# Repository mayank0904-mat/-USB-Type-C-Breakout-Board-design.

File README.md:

# USB Type-C Breakout Board

## Description
A compact USB Type-C breakout board designed using KiCad.

## Features
- USB Type-C Connector
- Through-hole breakout pins
- DRC Clean Design
- Gerber Files Included

## Software Used
- KiCad

## Author
Mayank Mathur

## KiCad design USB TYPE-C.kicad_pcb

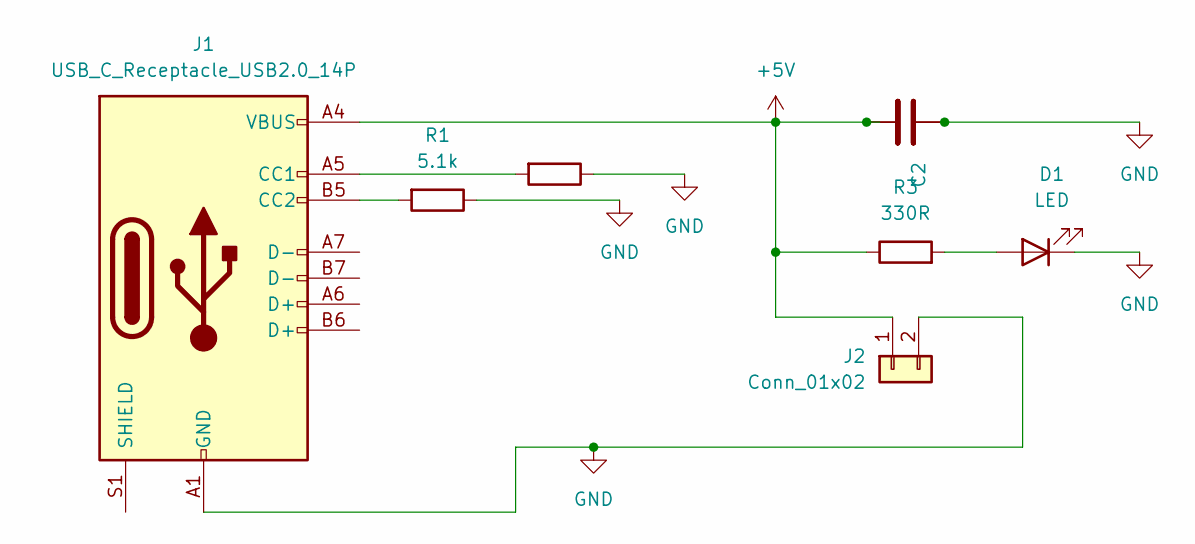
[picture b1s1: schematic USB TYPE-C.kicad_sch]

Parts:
C1: C; C_0805_2012Metric
C2: 10uf; C_0805_2012Metric
D1: LED; LED_0805_2012Metric
J1: USB_C_Receptacle_USB2.0_14P; USB_C_Receptacle_HRO_TYPE-C-31-M-12
J2: Conn_01x02; PinHeader_1x02_P2.54mm_Vertical
R1, R2: 5.1k; R_0805_2012Metric
R3: 330R; R_0805_2012Metric

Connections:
+5V: C1.2, C2.2, J1.A4 (VBUS), J1.A9 (VBUS), J1.B4 (VBUS), J1.B9 (VBUS), J2.1, R3.1
GND: C1.1, C2.1, D1.1 (K), J1.A1 (GND), J1.A12 (GND), J1.B1 (GND), J1.B12 (GND), J2.2, R1.1, R2.1
unnamed: D1.2 (A), R3.2
unnamed: J1.A5 (CC1), R2.2
unnamed: J1.B5 (CC2), R1.2

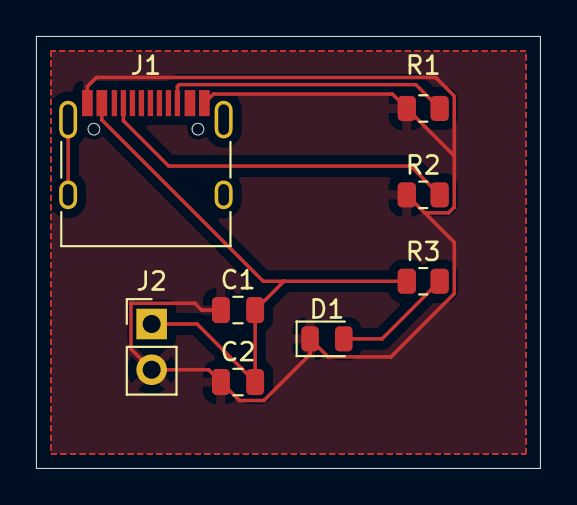
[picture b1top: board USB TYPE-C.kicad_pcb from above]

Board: 2 copper layers, 28.0 x 24.0 mm, 8 parts (0 on the bottom side), 5 nets.

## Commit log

2026-06-09 Initial Commit - USB Type-C Breakout Board
